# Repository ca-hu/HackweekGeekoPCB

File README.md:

# HackweekGeekoPCB

PCB of the Hackweek "Train of thought" Logo that blinks

The windows of the train have the copper layer and the mask removed, so the LEDs
will shine from behind the windows and make a blinking party train.

The loop above the head of the Geeko is a hanger so you can clip it onto your regular conference badges.

Link to Hackweek 2025 project:

https://hackweek.opensuse.org/25/projects/the-led-geeko-develop-a-diy-kit-for-a-wearable-led-geeko-badge

## BOM

- 4x RGB ~3V LEDs with inbuilt limiting resistor
- 1x SMD Button
- 1x CR2032 Battery Holder (SMD)
- 1x CR2032 Battery

## References

- I used the repository by blinkyparts as reference and also used their footprint library: https://github.com/blinkyparts/unicorn
- The Hackweek logo was edited to work for svg2mod and is taken from: https://hackweek.opensuse.org/img/HW24/

## Pictures

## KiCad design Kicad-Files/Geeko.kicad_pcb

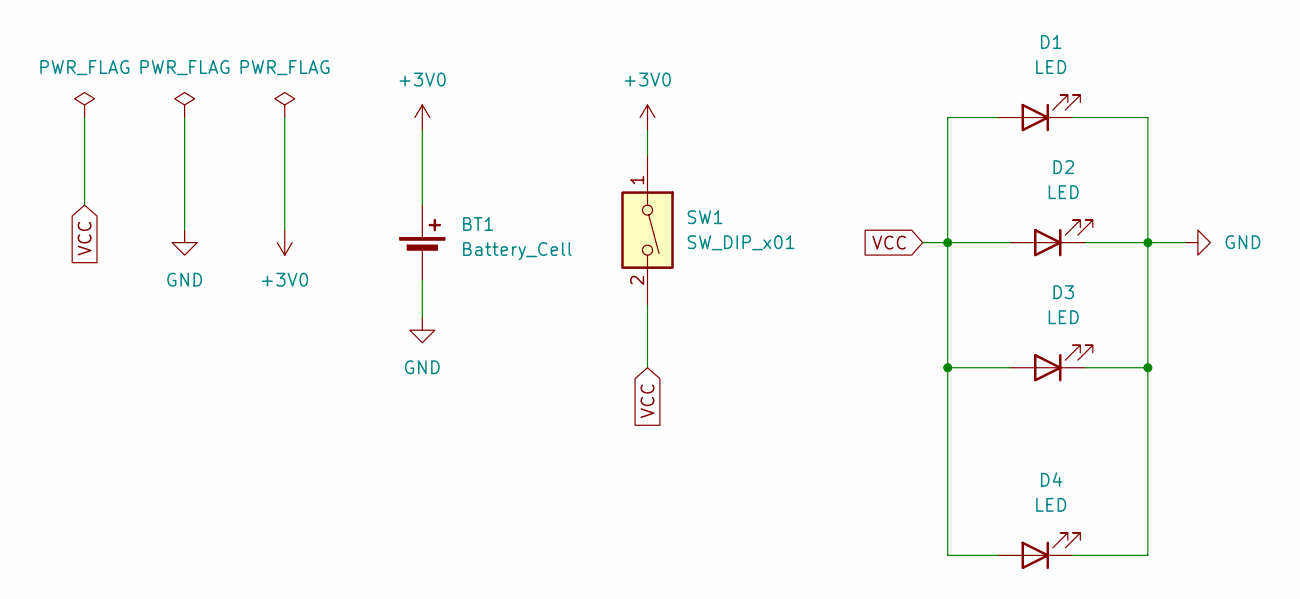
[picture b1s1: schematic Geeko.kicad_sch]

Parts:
BT1: Battery_Cell; BatteryHolder_Keystone_1060_1x2032
D1, D2, D3, D4: LED; 5mm_SMD-Pad
SW1: SW_DIP_x01; Push_Button

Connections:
+3V0: BT1.1 (+), SW1.1
GND: BT1.2 (-), D1.1 (K), D2.1 (K), D3.1 (K), D4.1 (K)
VCC: D1.2 (A), D2.2 (A), D3.2 (A), D4.2 (A), SW1.2

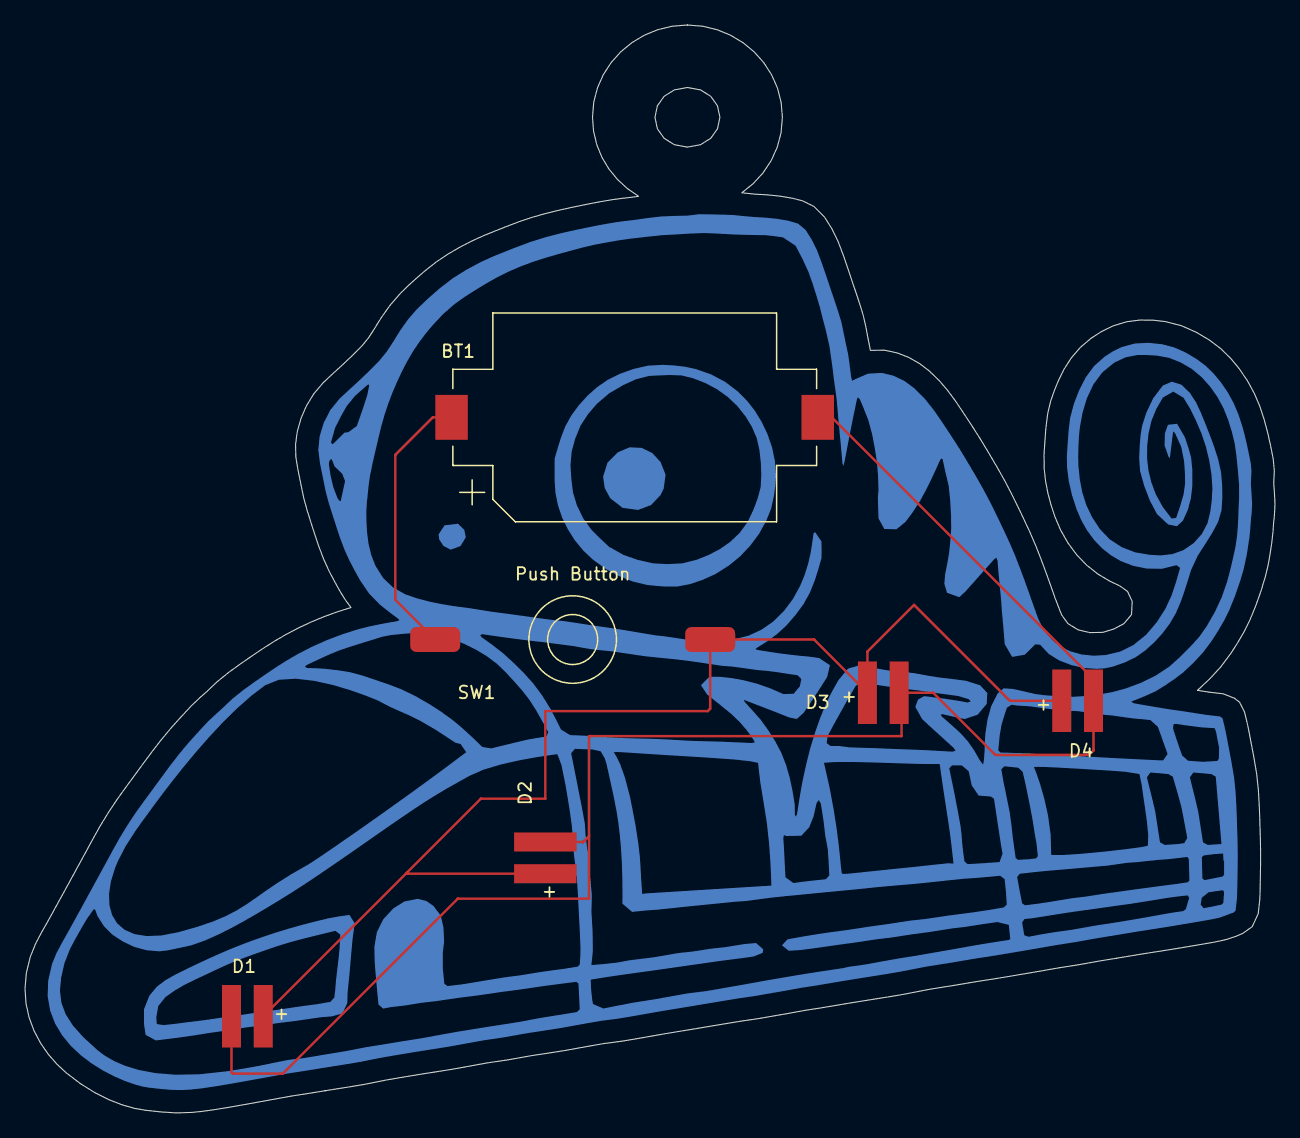
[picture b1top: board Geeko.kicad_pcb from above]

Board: 2 copper layers, 100.0 x 87.0 mm, 7 parts (1 on the bottom side), 3 nets.

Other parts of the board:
svg2mod: G***; GeekoInkscapeSVGDone_with_hanger

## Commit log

2025-12-04 Add final Kicad files
2025-12-04 Add final SVG files
2025-12-04 Add final kicad_mod files
2025-12-04 Add Screenshots
2025-12-04 Add Hackweek number
2025-12-17 Add Pictures of assembled PCB
